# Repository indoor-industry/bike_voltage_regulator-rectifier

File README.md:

Schematic, PCB design and 3D-printable case for a voltage regulator-rectifier designed for foot-crank motorbikes without batteries and a one wire accessories stator output.

For a bike with a battery, resistors R8 and R10 must be changed in accordance with the datasheet of the differential comparator (LM2903).
In the presence of a battery, the electrolytic capacitors can be removed for the sake of compactness. Additionally, a fifth input acting as an ignition turn-on switch should be added to avoid the regulator from slowly depleting the battery. All this is not necessary for batteryless bikes.

Output current may be limited by heat dissipation capabilities, the case is designed for the PCB to be immersed in resin or gel once inside it. Further testing is required.

The REF net is a stable 2.495V reference for the comparator. Right now the R8/R9 voltage divider scales down the output voltage at the other input of the comparator by 0.188. Such that it crosses the stable reference when the output voltage of the regulator is around   2.495V / 0.188 = 13.27V.
This implies that to change the regulation treshold one could, for example, replace R8 with a 24kOhm resistor and achieve a treshold of around 14.26V.

R10 adds hysteresis to the comparator to make it more stable and give a regulation band instead of a precise value. A higher R10 can give a more narrow band.

The two TO-220 packaged components have different nets connected to their tabs, if adding a heatsing to them, isolate the tabs from it and GND.

IMPORTANT: for single wire stators, the other wire is wired to the chassis, then one of the AC inputs to the regulator goes to the chassis as well and the the negative DC output should not be wired to the chassis to avoid losing full bridge rectification.
If the stator has 2-wires coming out of it and neither goes to the chassis, the negative DC output of the regulator can go to the chassis of the bike.

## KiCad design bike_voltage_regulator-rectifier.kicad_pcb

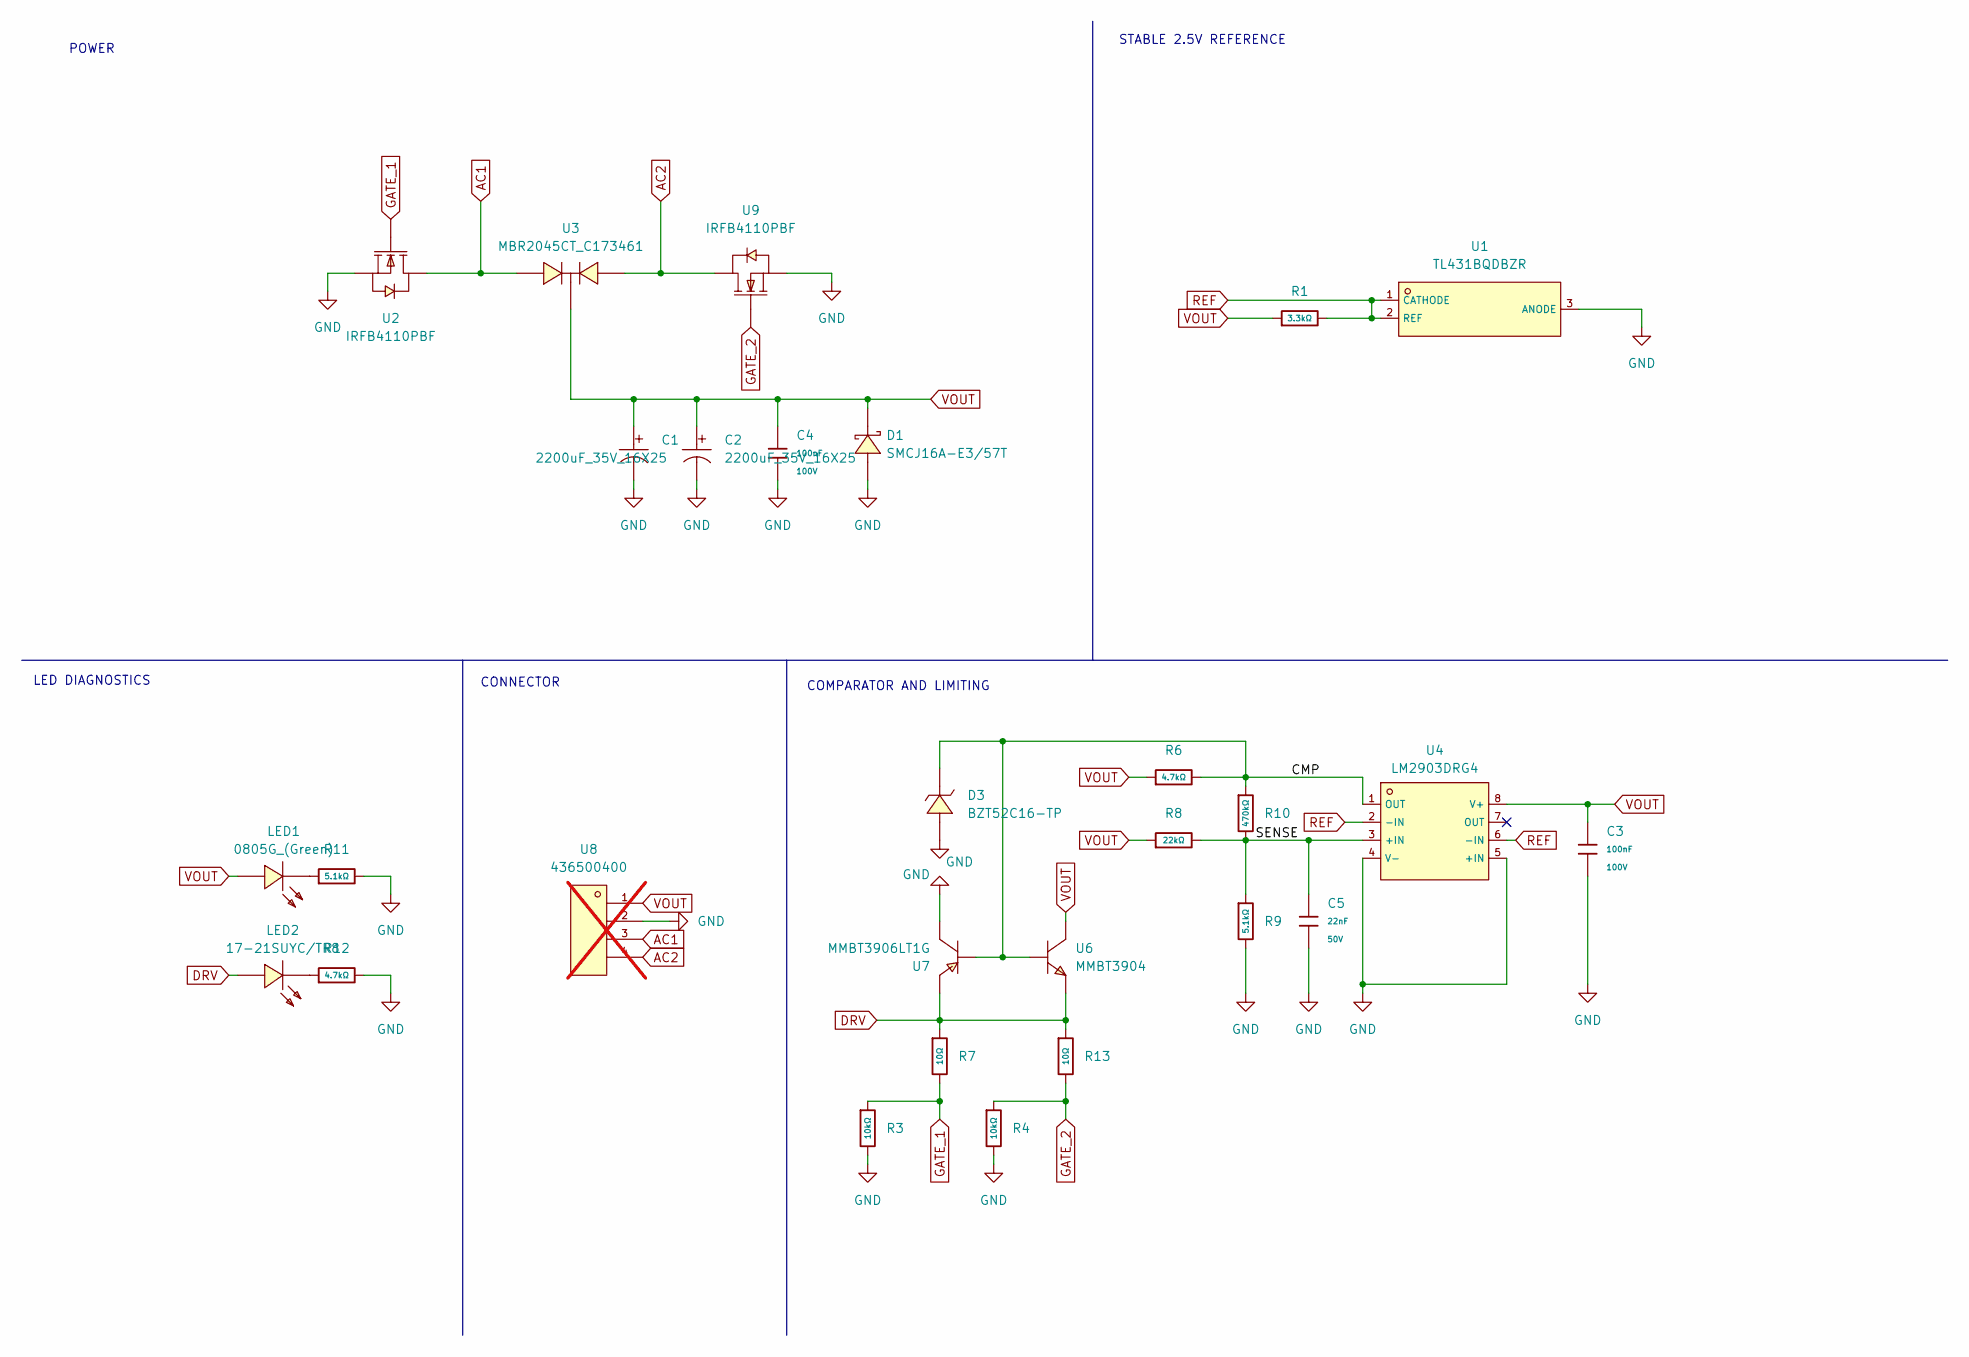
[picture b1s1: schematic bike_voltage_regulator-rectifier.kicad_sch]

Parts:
C1, C2: 2200uF_35V_16X25; CAP-TH_BD16.0-P7.50-D1.2-FD; LCSC C2763
C3, C4: 100nF; C_0805; Voltage Rated 100V; Tolerance ±10%; Part CL21B104KCFNNNE; LCSC C28233
C5: 22nF; C_0805; Voltage Rated 50V; Tolerance ±10%; Part CL21B223KBANNNC; LCSC C1729
D1: SMCJ16A-E3/57T; SMC_L6.9-W5.9-LS7.9-RD; LCSC C1976569
D3: BZT52C16-TP; SOD-123_L2.8-W1.8-LS3.7-RD; LCSC C668894
LED1: 0805G_(Green); LED0805-R-RD; LCSC C2297
LED2: 17-21SUYC/TR8; LED0805-R-RD; LCSC C2296
R1: 3.3kΩ; R_0805; Overload Voltage (Max) 150V; Tolerance ±1%; Part 0805W8F3301T5E; LCSC C26010
R3, R4: 10kΩ; R_0805; Overload Voltage (Max) 150V; Tolerance ±1%; Part 0805W8F1002T5E; LCSC C17414
R6, R12: 4.7kΩ; R_0805; Overload Voltage (Max) 150V; Tolerance ±1%; Part 0805W8F4701T5E; LCSC C17673
R7, R13: 10Ω; R_0805; Overload Voltage (Max) 150V; Tolerance ±1%; Part 0805W8F100JT5E; LCSC C17415
R8: 22kΩ; R_0805; Overload Voltage (Max) 150V; Tolerance ±1%; Part 0805W8F2202T5E; LCSC C17560
R9, R11: 5.1kΩ; R_0805; Overload Voltage (Max) 150V; Tolerance ±1%; Part 0805W8F5101T5E; LCSC C27834
R10: 470kΩ; R_0805; Overload Voltage (Max) 150V; Tolerance ±1%; Part 0805W8F4703T5E; LCSC C17709
U1: TL431BQDBZR; SOT-23-3_L2.9-W1.6-P1.90-LS2.8-BR; LCSC C190245
U2, U9: IRFB4110PBF; TO-220-3_L10.0-W4.5-P2.54-L; LCSC C2650
U3: MBR2045CT_C173461; TO-220AB-3_L10.4-W4.6-P2.54-T; LCSC C173461
U4: LM2903DRG4; SOIC-8_L5.0-W4.0-P1.27-LS6.0-BL; LCSC C7549
U6: MMBT3904; SOT-23-3_L2.9-W1.3-P1.90-LS2.4-BR; LCSC C20526
U7: MMBT3906LT1G; SOT-23-3_L2.9-W1.3-P1.90-LS2.4-BR; LCSC C53444
U8: 436500400; CONN-TH_4P-P3.00_L8.9-W15.7-EH4.7; LCSC C277684; not fitted

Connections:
/CMP: D3.1 (C), R6.2, R10.1, U4.1 (OUT), U6.1 (B), U7.1 (B)
/SENSE: C5.1, R8.2, R9.1, R10.2, U4.3 (+IN)
AC1: U2.2 (D), U3.1 (A), U8.3
AC2: U3.3 (A), U8.4, U9.2 (D)
DRV: LED2.1 (+), R7.1, R13.1, U6.2 (E), U7.2 (E)
GATE_1: R3.1, R7.2, U2.1 (G)
GATE_2: R4.1, R13.2, U9.1 (G)
GND: C1.2, C2.2, C3.2, C4.2, C5.2, D1.2 (A), D3.2 (A), R3.2, R4.2, R9.2, R11.2, R12.2, U1.3 (ANODE), U2.3 (S), U4.4 (V-), U4.5 (+IN), U7.3 (C), U8.2, U9.3 (S)
unnamed: LED1.2 (K), R11.1
unnamed: LED2.2 (-), R12.1
REF: R1.2, U1.1 (CATHODE), U1.2 (REF), U4.2 (-IN), U4.6 (-IN)
VOUT: C1.1, C2.1, C3.1, C4.1, D1.1 (K), LED1.1 (A), R1.1, R6.1, R8.1, U3.2 (C), U4.8 (V+), U6.3 (C), U8.1

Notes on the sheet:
STABLE 2.5V REFERENCE
CONNECTOR
POWER
LED DIAGNOSTICS
COMPARATOR AND LIMITING

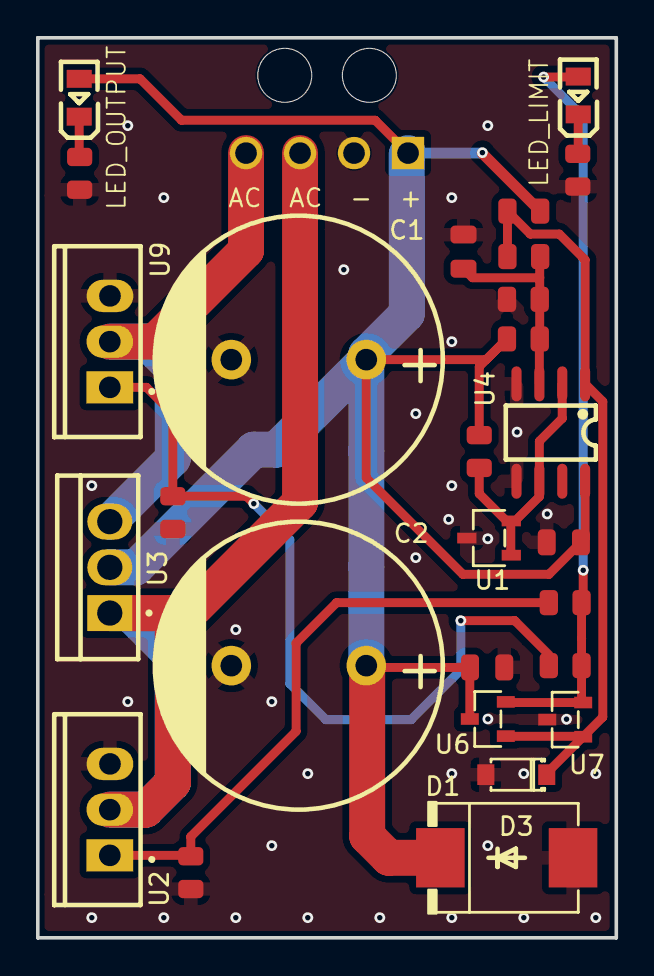
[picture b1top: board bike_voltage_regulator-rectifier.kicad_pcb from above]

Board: 2 copper layers, 32.1 x 50.0 mm, 28 parts (1 on the bottom side), 12 nets.
